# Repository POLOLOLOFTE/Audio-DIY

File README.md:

# Audio-DIY
An audio console where you can play with real time music!

## Descpription:
This is an Audio modificator in real time so you can controll how the audio sounds and give it some DJ style effects and it's open source so you can download the premade code or just code it yourself however you want

> **Note:** This is NOT a toy but neather a professional equipment.

this work with a 'ESP32 DevKit V1 30pin' and another board called codec and it's the board that take the analog input and convert it in digital numbers: 0 and 1

### Reasons:

i made this because i love music and i use to "play" with an old amplificators settings: there was only a filter for low and high frequences sound😭

## Assebly
it's preatty simple you gotta to soder with a sodering iron all of the things: like resistors, capacitors and screw connectors.

i have tryed to make it easy as possible but the controllers for the potenziometers is not soderable trough board so it won't be as easy as the other components

the rest is not that kind of easy but still simple when you know how it works:

you gotta connect all the buttons, potenziometers, leds;

trough some wire and you have to be near the schematic of the wires if you don't memorize it

and after this work you have to connect the mess (mine is going to be for sure it) to the pcb by the 22 screw connector

> **REMEMBER:** Lable every wire that gose in the pcb! with a number and a letter (for example P2: it's the second potenziometer).

for just not have all the wire and board hanging there you can print on a 3d printer the customizable at pcb-extra/3d/customizable case

and you have included all of the pieces and the 3d model.

for the case you have to go to my other reposty: freedigital amp case and you got the instructions for mounting it. but this board hasn't got any screw so it's mounted with hot glue(i know it's not professional but it work well)
an then there are the buttons (i choose to use some bipolar metal ones: they look sick) and potenziometers that goes in with the screw and the leds: just hot glue them

## INPUT and OUTPUT
the board has got 2 inputs:

the usb type c of the esp32 Devkit V1 30pin (for power)

the jack (the one soder on the board)

and it has got one output:

the jack on the other card (Analog Codec)

## Settings
The sound is controlled with 6 switch and 8 potenziometers, and they work all indipendently to others so your code can be basically anything differnt and still works with all the switch and potenziometers

### Let's talk about buttons to press!
if you use the the default code here are the things that you can do:

if you press any button you arledy strarting to change the sound of the input but the real magic comes with the potenziometers and you take controll of the audio compleatlly

there is a single potenziometers for thoose sounds that controls the power:
- pitch changer
- flangers
- reverb
- echo

but there are two effects that have two potenziometers:

- filter high-low
  the first one control the low frequences (it can boost it or lower it)
  the second control the high frequences (it can boost it or lower it)
  the medium frequences are untouched

- shutter
  the first potenziometer control the time of thoose shut (how much time they stay)
  and the second control the pause between those shuts

## Gallery

# Components that you Need

| Piece | Quantity | Notes | Link | USD |
| :--- | :---: | :--- | :--- | :---: |
| **ESP32 DevKit V1 (30pin)** | 1 | Main brain | [eBay Best Offer](https://www.ebay.it/itm/266490362209) | 14.23 |
| **Analog Codec Module** | 1 | Analog codec | [PCB Artists Site](https://pcbartists.com/product/es8388-module/) | 16.79 |
| **ADS1115IDGS** | 2 | potenziometers controller | [Amazon](https://www.amazon.it/-/en/ADS1115IDGSR-ADS1115IDGST-ADS1115IDGS-ADS1115-MSOP10/dp/B0CRQWTRNL/ref=sr_1_1?crid=3A7DLQN7I903N&dib=eyJ2IjoiMSJ9.-TmIbu7YQJw4iThlc6OG7MWgpj6EB_HSH48wNqmVZONnfdk-r3KiK01sLE0pXHxF-g91VWozS64dN5ynV5B_7gTRlVeP80SvG5o6kZ8EeXDfm4AXq1NMQx5EuUOJW4f5hZnC9gTOGtNqXZ1vLr6--8VqCrM2nnEDV2sqoPslPDWQHNZFGwUWPSa1a-AoExBXTplhvIQLp9tFjpdFu_JAK7lKG3X4uck0JFiCnp2s8OXNujH90LfcE37R5i9vtuiafWzRcmp6w7TZ4ZgTYhNOqxK_yItWzCYx4bKpvucx_pc.o1-ewgyV3qJF_BI8BGCa-Ho__qsU65buIypSJFIkgu4&dib_tag=se&keywords=ADS1115IDGS&qid=1792947325&sprefix=ads1115idgs%2Caps%2C146&sr=8-1) | 16.01 |
| **Resistor220Ω - 330Ω** | 6 | resistor for the leds | [Amazon](https://www.amazon.it/-/en/gp/product/B0FP51H3ML/ref=ox_sc_act_title_5?smid=A2X2IS1I8BHRL9&psc=1) | 15.66 |
| **Unpolarized capacitor** | 2 | protection for the controllers | [Amazon](https://www.amazon.it/-/en/gp/product/B07Y7PHY91/ref=ox_sc_act_title_9?smid=A3JM63OQAICKNV&psc=1) | 10.06 |
| **Polarized capacitor** | 2 | 10µF | [Amazon](https://www.amazon.it/TUNOTYUE-Electrolytic-Capacitors-Aluminum-Capacitor/dp/B0G2RY2BSH/ref=sr_1_1_sspa?crid=2CMKG581YDDUB&dib=eyJ2IjoiMSJ9.hzyaSPMoM8UhoWIptWNiW6G1ByCsDW-fX1Y78nOgJteIzrt-ga4Y0Wzr1AeJ893IjKJKRG0Q-MU_greb-UPTFb1oTTV7A_xKjiFIupc53l08Mb1fv9mMQs5gXCBuczoo5EgjF2RbquK0QHhrpx28v6KynAJ9Z2j0xiX9d6wYOMIiQGtZq3MqOp8xTvxdtciF26dqlxtNkBuUVuylpYMfEho5vOQ-aiGJTmhC9xACjvkDxJ2_NxNiHPj-UsCgDH_cm2x82R-BsodixUEZn82E7Y9k0r-zQoXajgedLavJCTI.gBNOIevjQ0IQa8Sm-2RqyOmjishg9t3M5NQw-km7WHU&dib_tag=se&keywords=capacitor+10uf+25v&qid=1792948425&sprefix=capacitor+10uf+25v%2Caps%2C148&sr=8-1-spons&aref=uQbY1q8Pl5&sp_csd=d2lkZ2V0TmFtZT1zcF9hdGY&psc=1) | 7.82 |
| **Screw connector** | 11x2 | connector for the accesorys | [Amazon](https://www.amazon.it/-/en/gp/product/B0FN6VYSFN/ref=ox_sc_act_title_8?smid=A2KWOEY1RHRC64&psc=1) | 12.30 |
| **Header Pin Female 1x10,1x15** | 2+2 | standard conectors 2.54mm | [Amazon](https://www.amazon.it/-/en/gp/product/B09NDMVD2C/ref=ox_sc_act_title_2?smid=A2FXWI8CY4G34J&psc=1) | 13.42 |
| **Jack Female** | 1 | Jack audio Wide without switch | [Amazon](https://www.amazon.it/-/en/gp/product/B0C4SV6GGS/ref=ox_sc_act_title_1?smid=A1TMZHY2SHKLH2&psc=1) | 19.46 |
| **Potenziometrs** | 8 | 10K potenziometers | [Amazon](https://www.amazon.it/-/en/gp/product/B07RHJZ979/ref=ox_sc_act_title_4?smid=AT0FJ7CZCB0G9&psc=1) | 11.18 |
| **Bipolar switches** | 6 | Switches used in racecars or airplanes | [Amazon](https://www.amazon.it/-/en/gp/product/B0GJN7GH6H/ref=ox_sc_act_title_3?smid=A2V9110KNWB97R&psc=1) | 9.25 |
| **LED** | 6 | LED standard 5mm | [Amazon](https://www.amazon.it/-/en/CESFONJER-500pcs-Emitting-Diffuser-Yellow/dp/B07DPJ23YT/ref=sr_1_37?crid=XZEDS0JP4E2B&dib=eyJ2IjoiMSJ9.IWaHpNgDMd8Aqs3IYhj34O66BZcgvMejt1W-sJlgLg5VYvXCjT1i-Qo6sT5UX5z1Vkh7h-rPIJF7w7bXKRT9yNzgOXVT_sMCTEhwaVdQcK7R-QR-ZqL3GEROBvxE-fju-tqfYjbFMVByLecUZt8rBpD-QQpcuPIYgGm_XH2h7ucs__5ha7a-pwbaMqnTLsln-Eea8YbCn4mcby-hXiz8kMpZAvMNrZhaO9aRDUQIA9IG20oFuBItBYIPe4QQ8i_ySTk37-TOvAgFNocJqGzd1c5bd24fr2TU_Xe9J8UhwNw.fy-LiWBKteqsv5HQnHX_2Hs5eu9_gWXX_ik8kk5EbeA&dib_tag=se&keywords=leds&qid=1792947888&sprefix=leds%2Caps%2C207&sr=8-37) | 14 |
| **Main PCB** | 1 | the one in the main folder | you can make it yourself or let it make from: (ex. JLCPCB / PCBWay) | 5.00/10 |
| **Soder** | 1 | For soder everything | you can buy it even localy | Variable |
| **Wire** | A bit for connecting things togheder | You can get it everywere | every type is great | Variable |

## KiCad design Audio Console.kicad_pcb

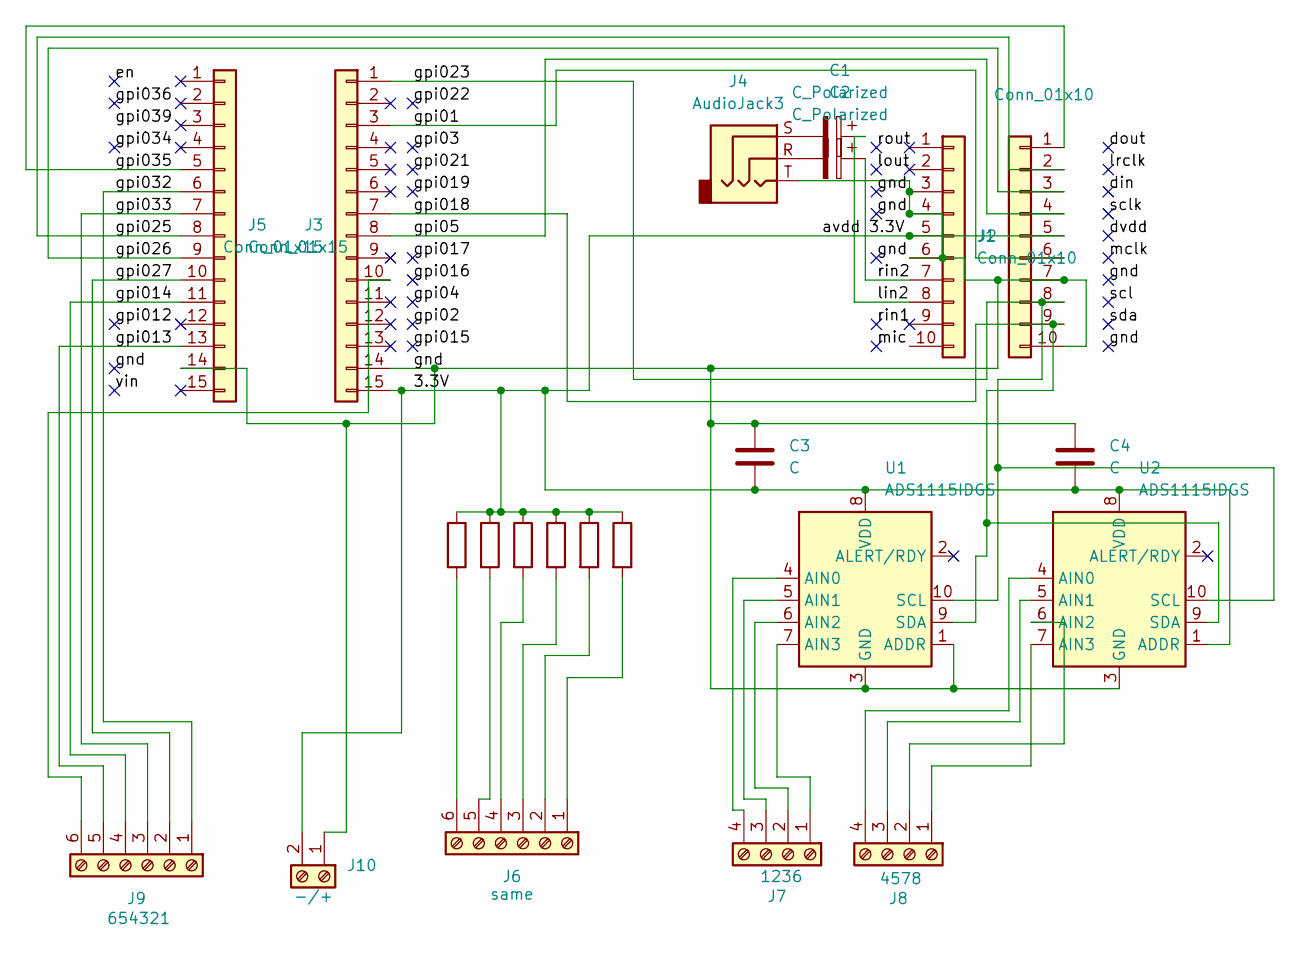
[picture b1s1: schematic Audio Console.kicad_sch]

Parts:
C1, C2: C_Polarized; CP_Radial_D5.0mm_P2.00mm
C3, C4: C; C_Disc_D5.0mm_W2.5mm_P5.00mm
J1, J2: Conn_01x10; PinSocket_1x10_P2.54mm_Vertical
J3, J5: Conn_01x15; PinSocket_1x15_P2.54mm_Vertical
J4: AudioJack3; Jack_3.5mm_CUI_SJ1-3523N_Horizontal
J6: same; TerminalBlock_Phoenix_MKDS-1,5-6-5.08_1x06_P5.08mm_Horizont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
J7: 1236; TerminalBlock_Phoenix_MKDS-1,5-4-5.08_1x04_P5.08mm_Horizont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
J8: 4578; TerminalBlock_Phoenix_MKDS-1,5-4-5.08_1x04_P5.08mm_Horizont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
J9: 654321; TerminalBlock_Phoenix_MKDS-1,5-6-5.08_1x06_P5.08mm_Horizont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
J10: -/+; TerminalBlock_Phoenix_MKDS-1,5-2-5.08_1x02_P5.08mm_Horizont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
R1, R2, R3, R4, R5, R6: R; R_Axial_DIN0207_L6.3mm_D2.5mm_P7.62mm_Horizontal
U1, U2: ADS1115IDGS; TSSOP-10_3x3mm_P0.5mm

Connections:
/3.3V: C3.2, C4.2, J1.5, J2.5, J3.15, J10.2, R1.1, R2.1, R3.1, R4.1, R5.1, R6.1, U1.8 (VDD), U2.1 (ADDR), U2.8 (VDD)
/gnd: C3.1, C4.1, J1.3, J1.4, J1.6, J2.7, J2.10, J3.14, J4.T, J5.14, J10.1, U1.1 (ADDR), U1.3 (GND), U2.3 (GND)
/gpi01: J2.6, J3.3
/gpi05: J2.4, J3.8
/gpi013: J5.13, J9.5
/gpi014: J5.11, J9.4
/gpi018: J2.9, J3.7, U1.9 (SDA), U2.9 (SDA)
/gpi023: J2.8, J3.1, U1.10 (SCL), U2.10 (SCL)
/gpi025: J2.2, J5.8
/gpi026: J2.3, J5.9
/gpi027: J5.10, J9.2
/gpi032: J5.6, J9.1
/gpi033: J5.7, J9.3
/gpi035: J2.1, J5.5
/lin2: C1.1, J1.8
/rin2: C2.1, J1.7
unnamed: C1.2, J4.S
unnamed: C2.2, J4.R
unnamed: J3.10, J9.6
unnamed: J6.1, R6.2
unnamed: J6.2, R5.2
unnamed: J6.3, R4.2
unnamed: J6.4, R3.2
unnamed: J6.5, R2.2
unnamed: J6.6, R1.2
unnamed: J7.1, U1.7 (AIN3)
unnamed: J7.2, U1.6 (AIN2)
unnamed: J7.3, U1.5 (AIN1)
unnamed: J7.4, U1.4 (AIN0)
unnamed: J8.1, U2.7 (AIN3)
unnamed: J8.2, U2.6 (AIN2)
unnamed: J8.3, U2.5 (AIN1)
unnamed: J8.4, U2.4 (AIN0)

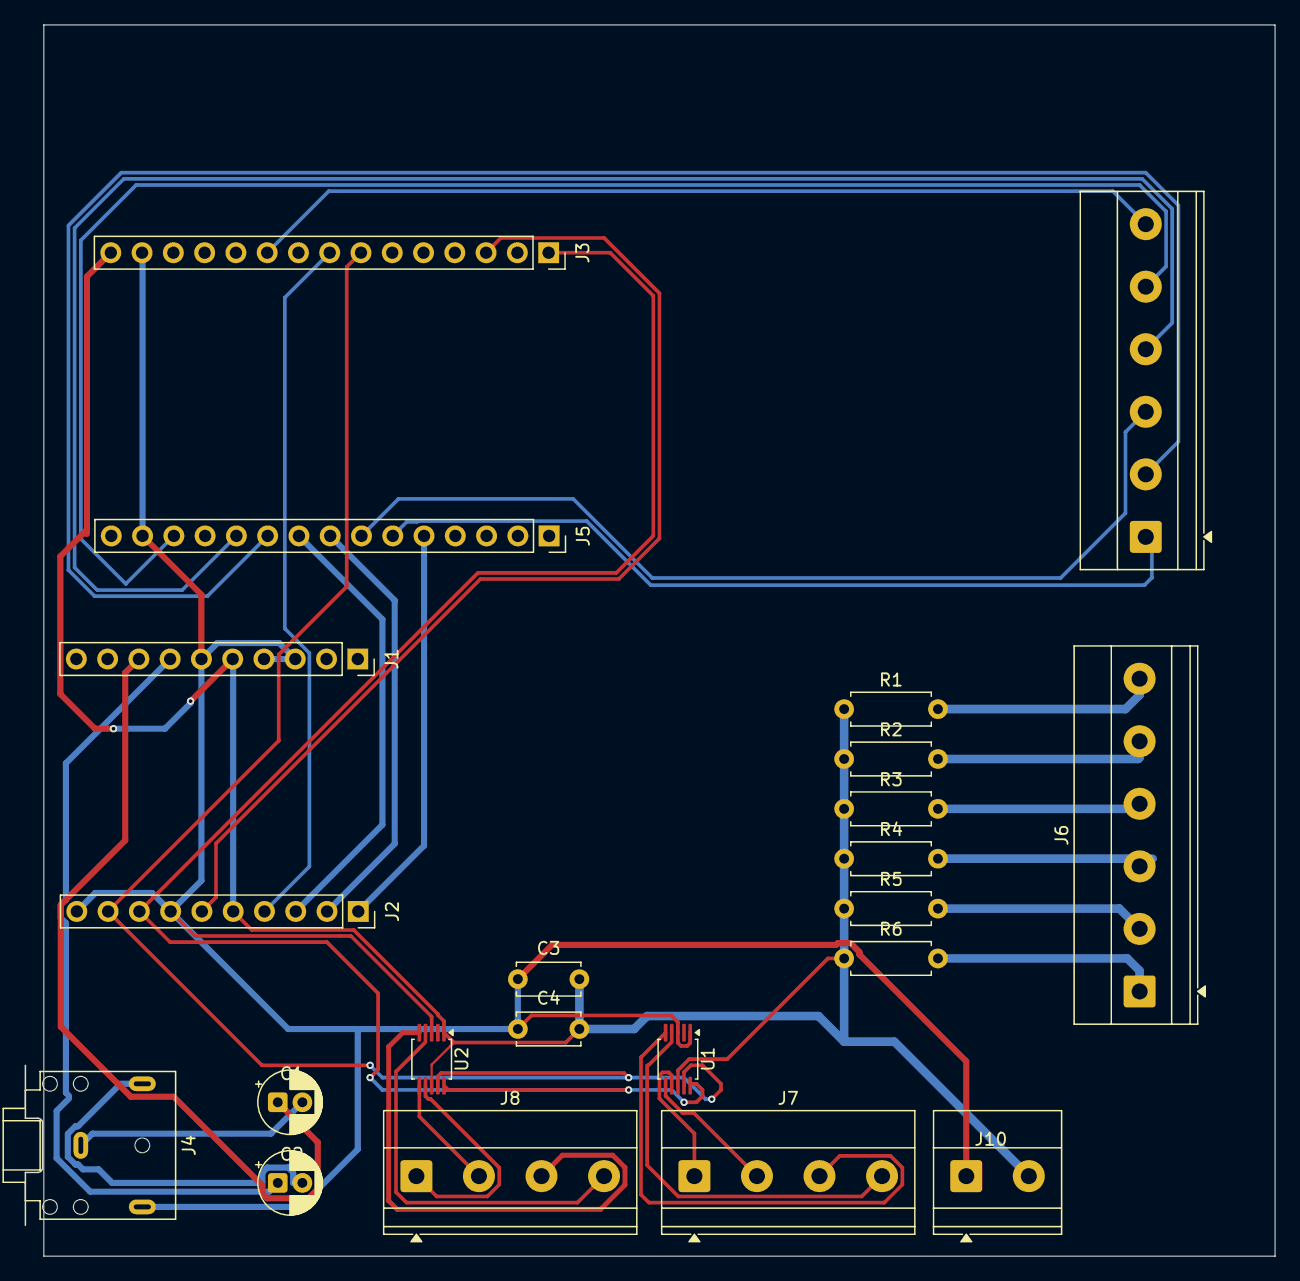
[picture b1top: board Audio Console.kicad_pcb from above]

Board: 2 copper layers, 101.5 x 100.0 mm, 22 parts (0 on the bottom side), 33 nets.
